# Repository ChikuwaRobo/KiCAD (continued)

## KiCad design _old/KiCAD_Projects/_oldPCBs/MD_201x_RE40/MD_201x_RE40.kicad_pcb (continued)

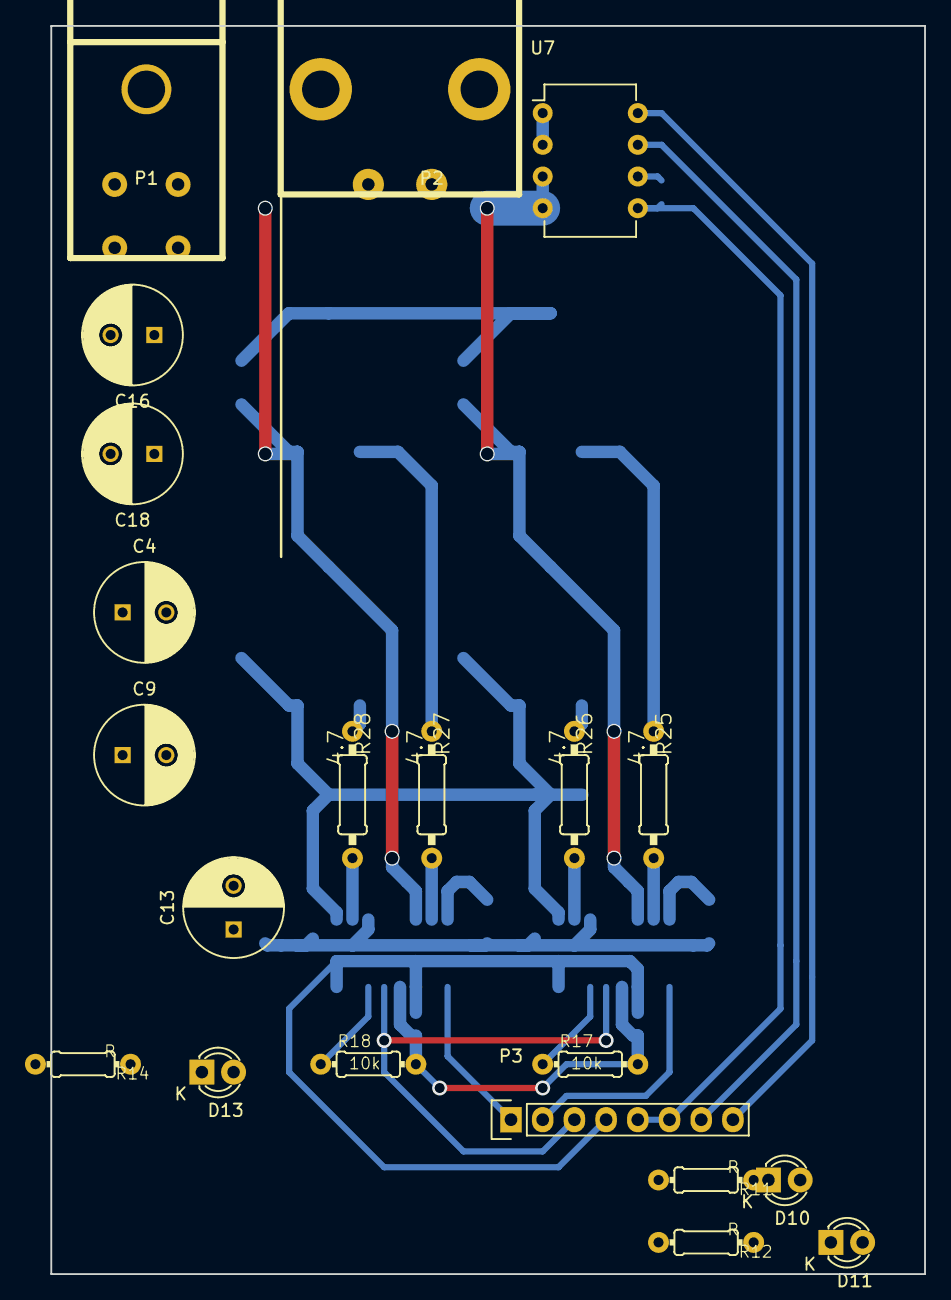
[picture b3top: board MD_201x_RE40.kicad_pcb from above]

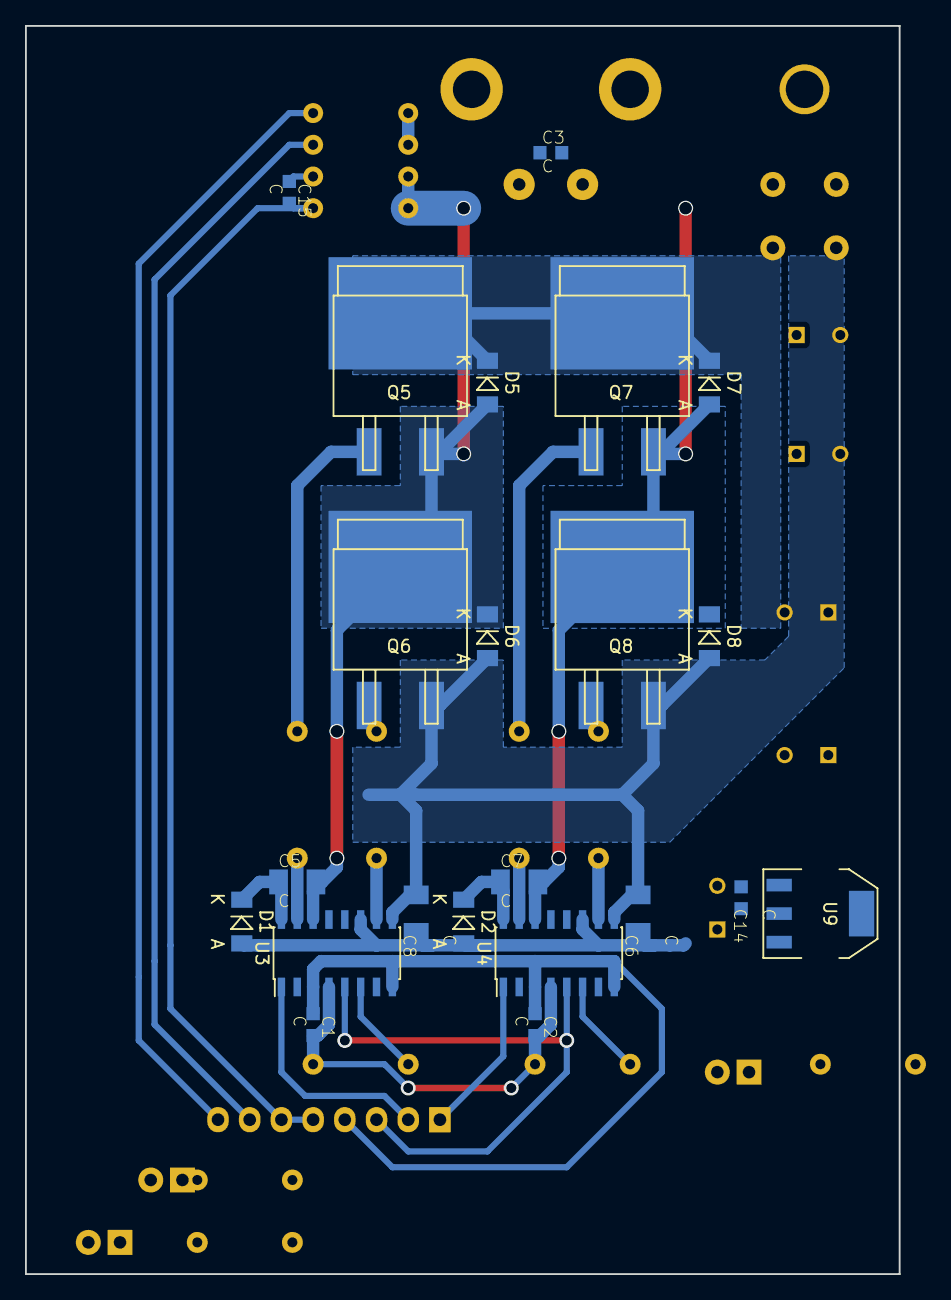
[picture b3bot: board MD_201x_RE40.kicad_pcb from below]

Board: 2 copper layers, 70.0 x 100.0 mm, 43 parts (22 on the bottom side), 29 nets.

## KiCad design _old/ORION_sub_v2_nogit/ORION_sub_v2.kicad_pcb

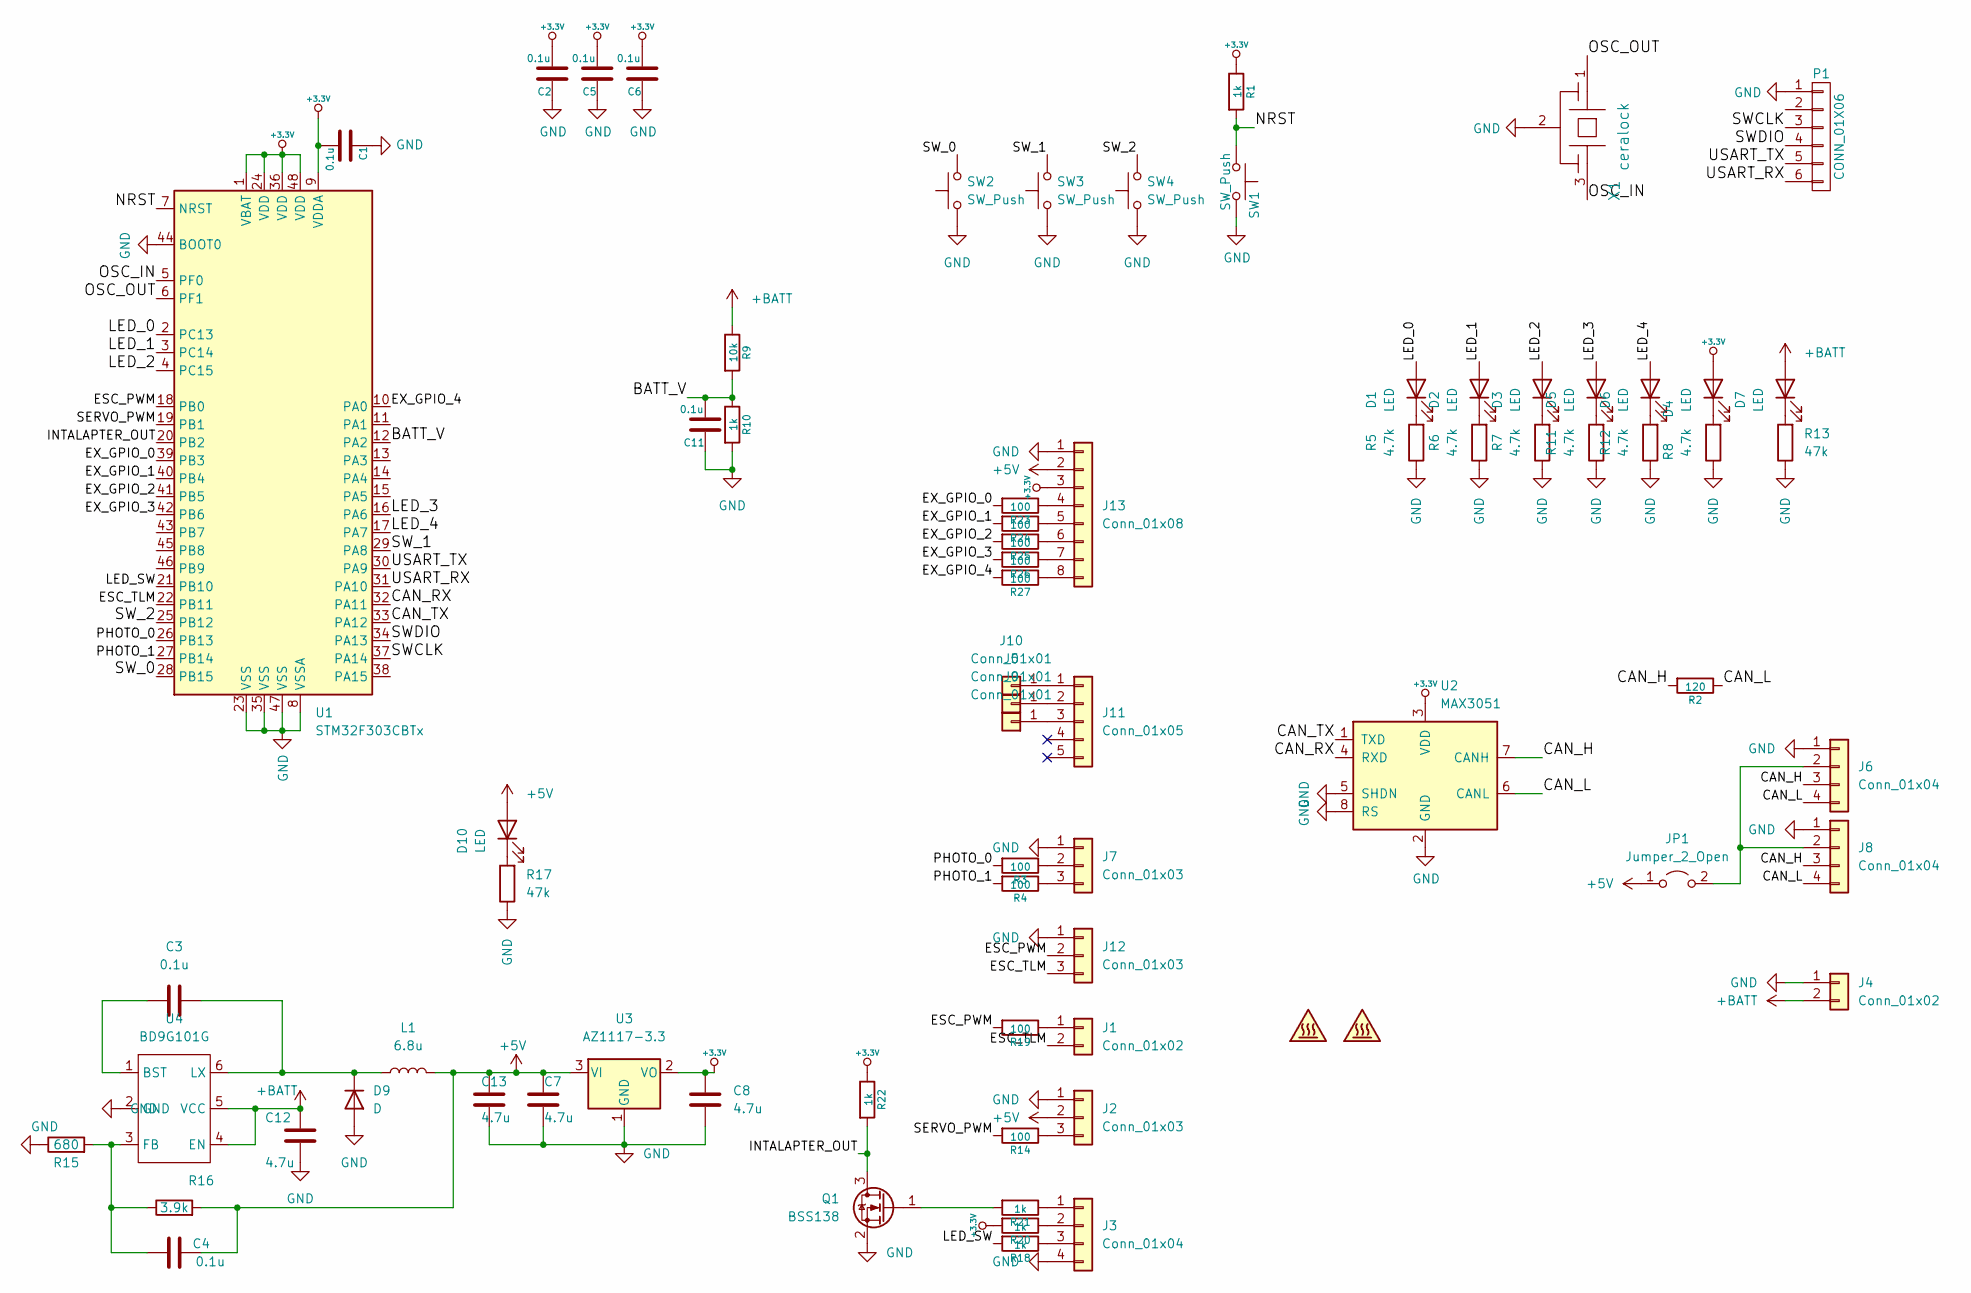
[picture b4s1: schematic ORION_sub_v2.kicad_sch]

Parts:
C1, C2, C5, C6, C11: 0.1u; C_0603_1608Metric
C3, C4: 0.1u; C_0402_1005Metric
C7, C8, C12, C13: 4.7u; C_1206_3216Metric
D1, D2, D3, D4, D5, D6, D7, D10: LED; LED_0603_1608Metric
D9: D; D_PowerDI-123
J1: Conn_01x02; Hirose_DF13-02P-1.25DSA_1x02_P1.25mm_Vertical
J2: Conn_01x03; JST_PH_S3B-PH-K_1x03_P2.00mm_Horizontal
J3, J6, J8: Conn_01x04; Hirose_DF13-04P-1.25DSA_1x04_P1.25mm_Vertical
J4: Conn_01x02; AMASS_XT30PW-M_1x02_P2.50mm_Horizontal
J5, J9, J10: Conn_01x01; WireSoldingPad_PowerTH
J7: Conn_01x03; Hirose_DF13-03P-1.25DSA_1x03_P1.25mm_Vertical
J11: Conn_01x05; 2053380003
J12: Conn_01x03; PinSocket_1x03_P2.54mm_Vertical
J13: Conn_01x08; Hirose_DF13-08P-1.25DSA_1x08_P1.25mm_Vertical
JP1: Jumper_2_Open; SolderJumper-2_P1.3mm_Open_RoundedPad1.0x1.5mm
L1: 6.8u; L_Taiyo-Yuden_NR-50xx
LG1: SYM_Hot_Small; ibis_logo_10x8mm_mask
LG2: SYM_Hot_Small; ibis_logo_10x8mm_silk
P1: CONN_01X06; ZH_B6B-ZR
Q1: BSS138; SOT-23
R1, R10, R18, R20, R21, R22: 1k; R_0603_1608Metric
R2: 120; R_0603_1608Metric
R3, R4, R14, R19, R23, R24, R25, R26, R27: 100; R_0603_1608Metric
R5, R6, R7, R8, R11, R12: 4.7k; R_0603_1608Metric
R9: 10k; R_0603_1608Metric
R13, R17: 47k; R_0603_1608Metric
R15: 680; R_0603_1608Metric
R16: 3.9k; R_0603_1608Metric
SW1, SW2, SW3, SW4: SW_Push; SW_Push_1P1T_NO_CK_KMR2
U1: STM32F303CBTx; LQFP-48_7x7mm_P0.5mm
U2: MAX3051; SO-8_3.9x4.9mm_P1.27mm
U3: AZ1117-3.3; SOT-23
U4: BD9G101G; SOT-23-6
X1: ceralock; Resonator_SMD_Murata_CSTxExxV-3Pin_3.0x1.1mm

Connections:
+3.3V: C1.2, C2.2, C5.2, C6.2, C8.1, D4.2 (A), J13.3, R1.1, R20.2, R22.1, U1.1 (VBAT), U1.9 (VDDA), U1.24 (VDD), U1.36 (VDD), U1.48 (VDD), U2.3 (VDD), U3.2 (VO)
+5V: C4.1, C7.1, C13.1, D10.2 (A), J2.2, J13.2, JP1.1 (A), L1.2, R16.2, U3.3 (VI)
+BATT: C12.1, D7.2 (A), J4.2, R9.1, U4.4 (EN), U4.5 (VCC)
/BATT_V: C11.2, R9.2, R10.1, U1.12 (PA2)
/CAN_H: J6.3, J8.3, R2.2, U2.7 (CANH)
/CAN_L: J6.4, J8.4, R2.1, U2.6 (CANL)
/CAN_RX: U1.32 (PA11), U2.4 (RXD)
/CAN_TX: U1.33 (PA12), U2.1 (TXD)
/ESC_PWM: J12.2, R19.2, U1.18 (PB0)
/ESC_TLM: J1.2, J12.3, U1.22 (PB11)
/EX_GPIO_0: R23.2, U1.39 (PB3)
/EX_GPIO_1: R24.2, U1.40 (PB4)
/EX_GPIO_2: R25.2, U1.41 (PB5)
/EX_GPIO_3: R26.2, U1.42 (PB6)
/EX_GPIO_4: R27.2, U1.10 (PA0)
/INTALAPTER_OUT: Q1.3 (D), R22.2, U1.20 (PB2)
/LED_0: D1.2 (A), U1.2 (PC13)
/LED_1: D2.2 (A), U1.3 (PC14)
/LED_2: D3.2 (A), U1.4 (PC15)
/LED_3: D5.2 (A), U1.16 (PA6)
/LED_4: D6.2 (A), U1.17 (PA7)
/LED_SW: R18.2, U1.21 (PB10)
/NRST: R1.2, SW1.1, U1.7 (NRST)
/OSC_IN: U1.5 (PF0), X1.3
/OSC_OUT: U1.6 (PF1), X1.1
/PHOTO_0: R3.2, U1.26 (PB13)
/PHOTO_1: R4.2, U1.27 (PB14)
/SERVO_PWM: R14.2, U1.19 (PB1)
/SWCLK: P1.3, U1.37 (PA14)
/SWDIO: P1.4, U1.34 (PA13)
/SW_0: SW2.2, U1.28 (PB15)
/SW_1: SW3.2, U1.29 (PA8)
/SW_2: SW4.2, U1.25 (PB12)
/USART_RX: P1.6, U1.31 (PA10)
/USART_TX: P1.5, U1.30 (PA9)
GND: C1.1, C2.1, C5.1, C6.1, C7.2, C8.2, C11.1, C12.2, C13.2, D9.2 (A), J2.1, J3.4, J4.1, J6.1, J7.1, J8.1, J12.1, J13.1, P1.1, Q1.2 (S), R5.1, R6.1, R7.1, R8.1, R10.2, R11.1, R12.1, R13.1, R15.1, R17.1, SW1.2, SW2.1, SW3.1, SW4.1, U1.8 (VSSA), U1.23 (VSS), U1.35 (VSS), U1.44 (BOOT0), U1.47 (VSS), U2.2 (GND), U2.5 (SHDN), U2.8 (RS), U3.1 (GND), U4.2 (GND), X1.2
unnamed: C3.1, D9.1 (K), L1.1, U4.6 (LX)
unnamed: C3.2, U4.1 (BST)
unnamed: C4.2, R15.2, R16.1, U4.3 (FB)
unnamed: D1.1 (K), R5.2
unnamed: D2.1 (K), R6.2
unnamed: D3.1 (K), R7.2
unnamed: D4.1 (K), R8.2
unnamed: D5.1 (K), R11.2
unnamed: D6.1 (K), R12.2
unnamed: D7.1 (K), R13.2
unnamed: D10.1 (K), R17.2
unnamed: J1.1, R19.1
unnamed: J2.3, R14.1
unnamed: J3.1, R21.1
unnamed: J3.2, R20.1
unnamed: J3.3, R18.1
unnamed: J6.2, J8.2, JP1.2 (B)
unnamed: J7.2, R3.1
unnamed: J7.3, R4.1
unnamed: J10.1, J11.1
unnamed: J5.1, J11.2
unnamed: J9.1, J11.3
unnamed: J13.4, R23.1
unnamed: J13.5, R24.1
unnamed: J13.6, R25.1
unnamed: J13.7, R26.1
unnamed: J13.8, R27.1
unnamed: Q1.1 (G), R21.2

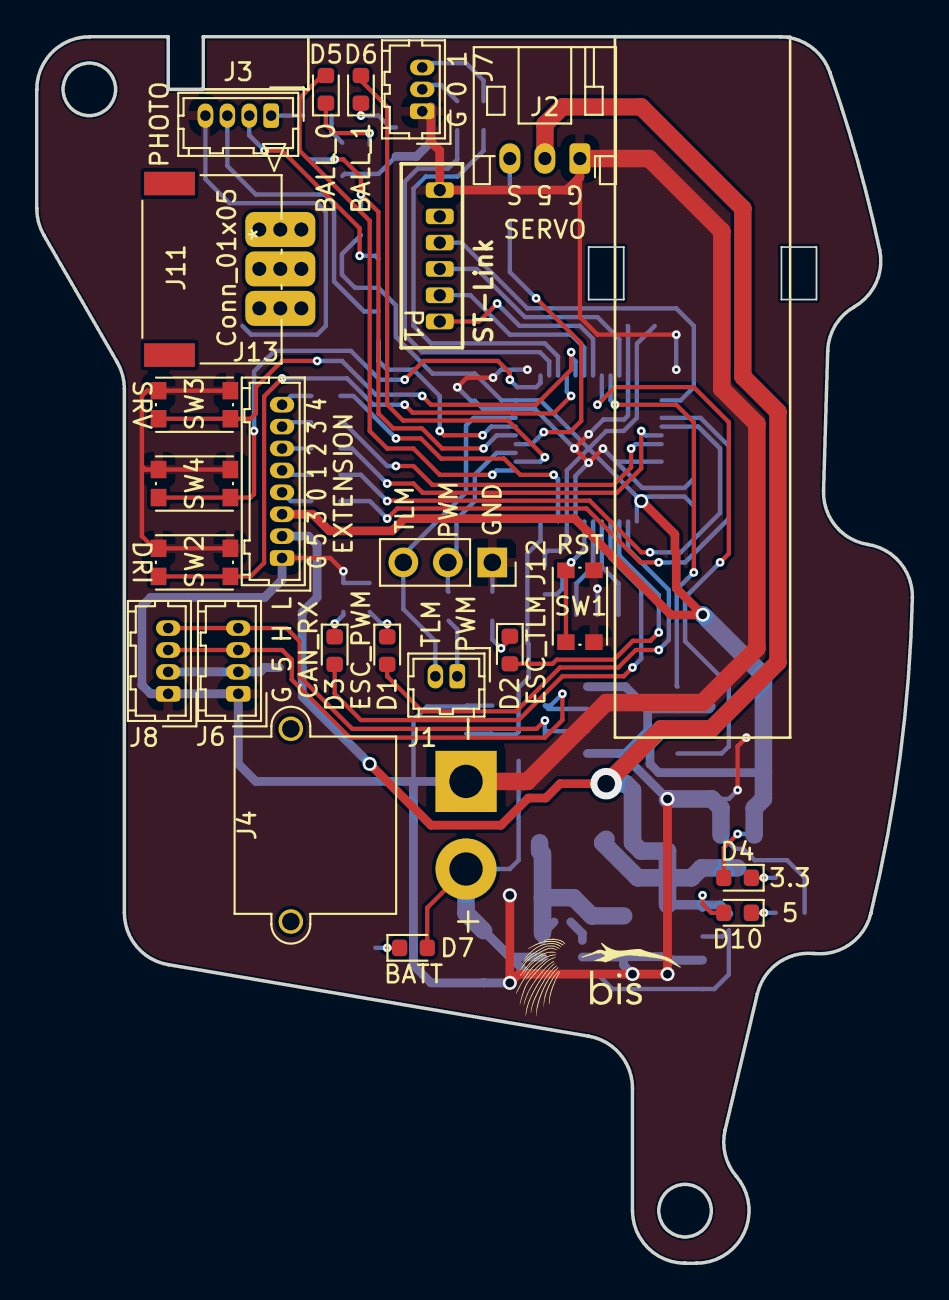
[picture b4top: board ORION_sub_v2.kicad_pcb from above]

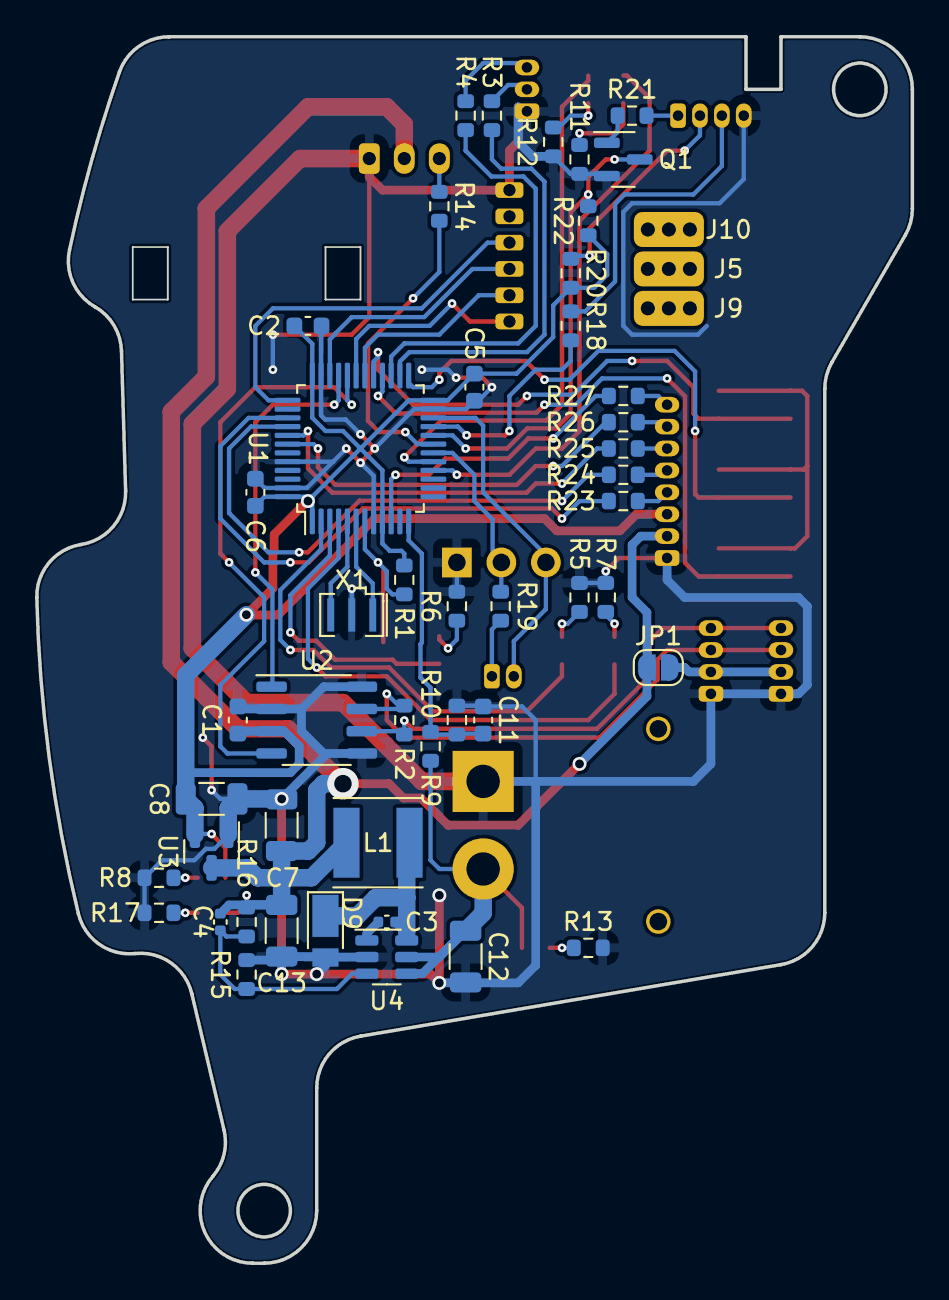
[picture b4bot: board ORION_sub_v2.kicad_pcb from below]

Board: 2 copper layers, 50.0 x 70.0 mm, 75 parts (50 on the bottom side), 64 nets.

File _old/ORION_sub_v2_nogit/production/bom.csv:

Designator,Footprint,Quantity,Value,LCSC Part #
"C1, C11, C2, C5, C6",C_0603_1608Metric,5,0.1u,
"C12, C13, C7, C8",C_1206_3216Metric,4,4.7u,
"C3, C4",C_0402_1005Metric,2,0.1u,
"D1, D10, D2, D3, D4, D5, D6, D7",LED_0603_1608Metric,8,LED,
D9,D_PowerDI-123,1,D,
J1,Hirose_DF13-02P-1.25DSA_1x02_P1.25mm_Vertical,1,Conn_01x02,
"J10, J5, J9",WireSoldingPad_PowerTH,3,Conn_01x01,
J11,2053380003,1,Conn_01x05,
J12,PinSocket_1x03_P2.54mm_Vertical,1,Conn_01x03,
J13,Hirose_DF13-08P-1.25DSA_1x08_P1.25mm_Vertical,1,Conn_01x08,
J2,JST_PH_S3B-PH-K_1x03_P2.00mm_Horizontal,1,Conn_01x03,
"J3, J6, J8",Hirose_DF13-04P-1.25DSA_1x04_P1.25mm_Vertical,3,Conn_01x04,
J4,AMASS_XT30PW-M_1x02_P2.50mm_Horizontal,1,Conn_01x02,
J7,Hirose_DF13-03P-1.25DSA_1x03_P1.25mm_Vertical,1,Conn_01x03,
JP1,SolderJumper-2_P1.3mm_Open_RoundedPad1.0x1.5mm,1,Jumper_2_Open,
L1,L_Taiyo-Yuden_NR-50xx,1,6.8u,
LG1,ibis_logo_10x8mm_mask,1,SYM_Hot_Small,
LG2,ibis_logo_10x8mm_silk,1,SYM_Hot_Small,
P1,ZH_B6B-ZR,1,CONN_01X06,
Q1,SOT-23,1,BSS138,
"R1, R10, R18, R20, R21, R22",R_0603_1608Metric,6,1k,
"R11, R12, R5, R6, R7, R8",R_0603_1608Metric,6,4.7k,
"R13, R17",R_0603_1608Metric,2,47k,
"R14, R19, R23, R24, R25, R26, R27, R3, R4",R_0603_1608Metric,9,100,
R15,R_0603_1608Metric,1,680,
R16,R_0603_1608Metric,1,3.9k,
R2,R_0603_1608Metric,1,120,
R9,R_0603_1608Metric,1,10k,
"SW1, SW2, SW3, SW4",SW_Push_1P1T_NO_CK_KMR2,4,SW_Push,
U1,LQFP-48_7x7mm_P0.5mm,1,STM32F303CBTx,
U2,SO-8_3.9x4.9mm_P1.27mm,1,MAX3051,
U3,SOT-23,1,AZ1117-3.3,
U4,SOT-23-6,1,BD9G101G,
X1,Resonator_SMD_Murata_CSTxExxV-3Pin_3.0x1.1mm,1,ceralock,

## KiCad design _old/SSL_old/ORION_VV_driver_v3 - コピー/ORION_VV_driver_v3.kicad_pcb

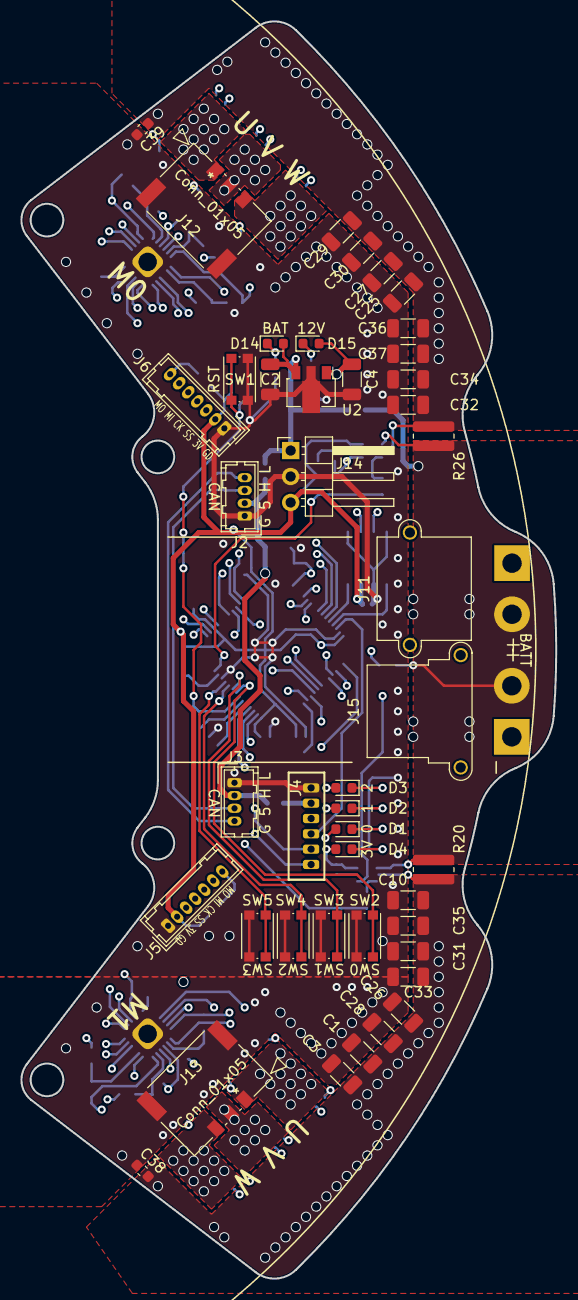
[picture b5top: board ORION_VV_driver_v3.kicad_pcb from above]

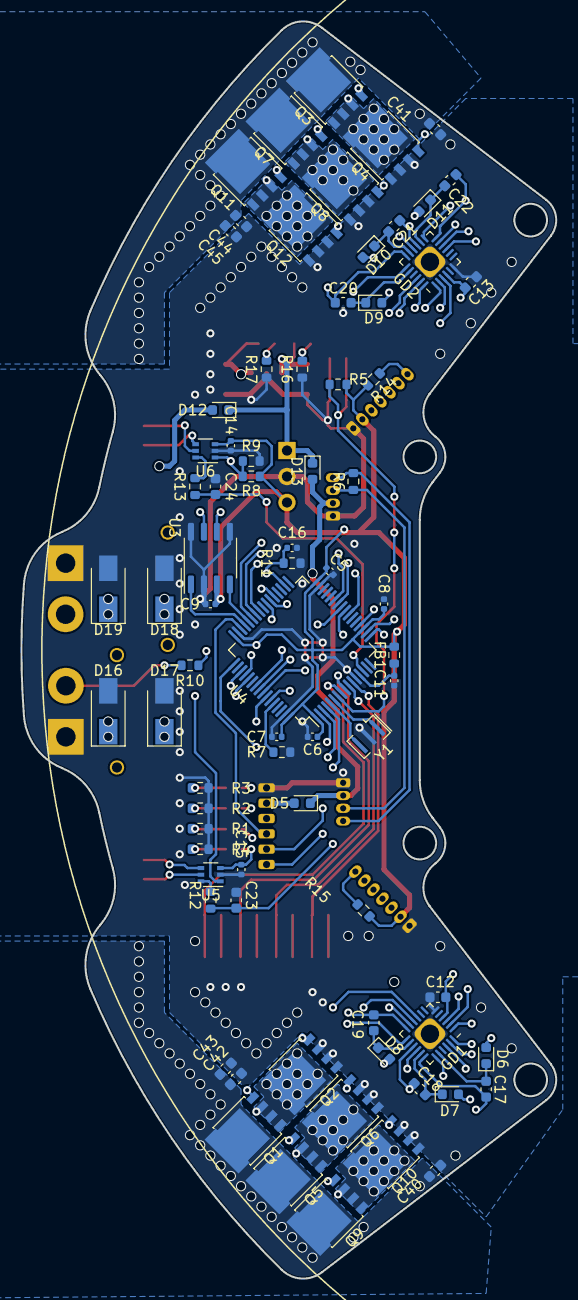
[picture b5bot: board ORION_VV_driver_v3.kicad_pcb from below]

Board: 4 copper layers, 52.4 x 123.1 mm, 119 parts (75 on the bottom side), 84 nets.

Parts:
C1, C2, C3, C4, C10, C25, C26, C27, C28, C29, C30, C31, C32, C33, C34, C35, C36, C37: 4.7u; C_1206_3216Metric
C5, C6, C7, C8, C9, C11, C14, C15, C16: 0.1u; C_0402_1005Metric
C12, C13, C38, C39, C40, C41, C42, C43, C44, C45: 0.1u; C_0603_1608Metric
C17, C18, C19, C20, C21, C22, C23, C24: 1u; C_0603_1608Metric
D1, D2, D3, D4, D14, D15: LED; LED_0603_1608Metric
D5, D6, D7, D8, D9, D10, D11, D12, D13: D; D_0603_1608Metric
D16, D17, D18, D19: D_Zener; D_SMA
FB1: FB100; R_0603_1608Metric
GD1, GD2: FD6288Q; QFN-24-1EP_4x4mm_P0.5mm_EP2.6x2.6mm_Thhole_v2
J2, J3: Conn_01x04; Hirose_DF13-04P-1.25DSA_1x04_P1.25mm_Vertical
J4: Conn_01x06; ZH_B6B-ZR
J5, J6: Conn_01x07; Hirose_DF13-07P-1.25DSA_1x07_P1.25mm_Vertical
J11: Conn_01x02; AMASS_XT30PW-M_1x02_P2.50mm_Horizontal
J12, J13: Conn_01x05; 2053380003
J14: Conn_01x03; PinHeader_1x03_P2.54mm_Horizontal
J15: Conn_01x02; AMASS_XT30PW-F_1x02_P2.50mm_Horizontal
Q1, Q2, Q3, Q4, Q5, Q6, Q7, Q8, Q9, Q10, Q11, Q12: IRF8721PBF-1; LFPAK56
R1, R2, R3, R4: 4.7k; R_0603_1608Metric
R5, R7, R11: 1k; R_0603_1608Metric
R6: 120; R_0603_1608Metric
R8, R9, R12, R13: 100; R_0603_1608Metric
R10, R14, R15: 10k; R_0603_1608Metric
R16, R17: 47k; R_0603_1608Metric
R20, R26: 10m; R_0815_2038Metric
SW1, SW2, SW3, SW4, SW5: SW_Push; SW_Push_1P1T_NO_CK_KMR2
U2: L78L15_SOT89; SOT-89-3
U3: MAX3051; SO-8_3.9x4.9mm_P1.27mm
U4: LQFP-64_10x10mm_P0.5mm
U5, U6: INA199; SOT-363_SC-70-6
Y1: Resonator; Resonator_SMD_Murata_CSTxExxV-3Pin_3.0x1.1mm

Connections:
+3V3: C5.2, C6.2, C7.2, C8.2, C9.2, C14.2, C15.2, D4.2 (A), FB1.1, J5.2, J6.2, J14.3, R5.2, R8.1, R14.2, R15.2, U3.3 (VDD), U4.1 (VBAT), U4.19 (VDD), U4.32 (VDD), U4.48 (VDD), U4.64 (VDD), U5.3 (VDD), U6.3 (VDD)
+5V: D5.1 (K), D13.2 (A), J2.2, J3.2
+12V: C4.2, C12.2, C13.2, D6.2 (A), D7.2 (A), D8.2 (A), D9.2 (A), D10.2 (A), D11.2 (A), D15.2 (A), GD1.4 (VCC), GD2.4 (VCC), U2.1 (OUT)
+BATT: D12.2 (A), D16.1 (K), D17.1 (K), D18.1 (K), D19.1 (K), J11.2, J15.2, R10.1, R20.1, R26.1, U5.4 (IN+), U6.4 (IN+)
/3V3_HARF_REF: R8.2, R9.1, U5.1 (REF), U6.1 (REF)
/BATT_V_SENS: C16.2, R10.2, R11.1, U4.34 (PB13)
/CAN_H: J2.3, J3.3, R6.1, U3.7 (CANH)
/CAN_L: J2.4, J3.4, R6.2, U3.6 (CANL)
/CAN_RX: U3.4 (RXD), U4.44 (PA11)
/CAN_TX: U3.1 (TXD), U4.45 (PA12)
/LED_0: D1.2 (A), U4.2 (PC13)
/LED_1: D2.2 (A), U4.3 (PC14)
/LED_2: D3.2 (A), U4.4 (PC15)
/M0_CS: C24.2, R13.1, U4.14 (PA0)
/M0_CSL: C25.1, C27.1, C29.1, C30.1, C32.1, C34.1, C36.1, C37.1, C39.2, C41.2, C44.2, C45.2, Q3.5 (D), Q7.5 (D), Q11.5 (D), R26.2, U6.5 (IN-)
/M0_U: C22.1, GD2.12 (VS3), J12.1, Q3.1 (S), Q3.2 (S), Q3.3 (S), Q4.5 (D)
/M0_UH: GD2.22 (HIN1), U4.41 (PA8)
/M0_UL: GD2.1 (LIN1), U4.23 (PA7)
/M0_V: C21.1, GD2.15 (VS2), J12.2, Q7.1 (S), Q7.2 (S), Q7.3 (S), Q8.5 (D)
/M0_VH: GD2.23 (HIN2), U4.42 (PA9)
/M0_VL: GD2.2 (LIN2), U4.26 (PB0)
/M0_W: C20.1, GD2.18 (VS1), J12.3, Q11.1 (S), Q11.2 (S), Q11.3 (S), Q12.5 (D)
/M0_WH: GD2.24 (HIN3), U4.43 (PA10)
/M0_WL: GD2.3 (LIN3), U4.27 (PB1)
/M1_CS: C23.2, R12.1, U4.20 (PA4)
/M1_CSL: C1.1, C3.1, C10.1, C26.1, C28.1, C31.1, C33.1, C35.1, C38.2, C40.2, C42.2, C43.2, Q1.5 (D), Q5.5 (D), Q9.5 (D), R20.2, U5.5 (IN-)
/M1_U: C19.1, GD1.12 (VS3), J13.1, Q1.1 (S), Q1.2 (S), Q1.3 (S), Q2.5 (D)
/M1_UH: GD1.22 (HIN1), U4.37 (PC6)
/M1_UL: GD1.1 (LIN1), U4.51 (PC10)
/M1_V: C18.1, GD1.15 (VS2), J13.2, Q5.1 (S), Q5.2 (S), Q5.3 (S), Q6.5 (D)
/M1_VH: GD1.23 (HIN2), U4.38 (PC7)
/M1_VL: GD1.2 (LIN2), U4.52 (PC11)
/M1_W: C17.1, GD1.18 (VS1), J13.3, Q9.1 (S), Q9.2 (S), Q9.3 (S), Q10.5 (D)
/M1_WH: GD1.24 (HIN3), U4.39 (PC8)
/M1_WL: GD1.3 (LIN3), U4.53 (PC12)
/NRST: R5.1, SW1.2, U4.7 (NRST)
/NSS_ENC0: J5.3, U4.58 (PB6)
/NSS_ENC1: J6.3, U4.59 (PB7)
/OSC_IN: U4.5 (PF0), Y1.3
/OSC_OUT: U4.6 (PF1), Y1.1
/SPI_CLK: J5.4, J6.4, U4.55 (PB3)
/SPI_MISO: J5.5, J6.5, U4.56 (PB4)
/SPI_MOSI: J5.6, J6.6, U4.57 (PB5)
/SW0: SW2.2, U4.8 (PC0)
/SW1: SW3.2, U4.9 (PC1)
/SW2: SW4.2, U4.10 (PC2)
/SW3: SW5.2, U4.11 (PC3)
/SWCLK: J4.3, U4.49 (PA14)
/SWDIO: J4.4, U4.46 (PA13)
/TEMP_0: J5.7, R15.1, U4.17 (PA3)
/TEMP_1: J6.7, R14.1, U4.18 (PF4)
/UART1_RX: J4.6, U4.25 (PC5)
/UART1_TX: J4.5, U4.24 (PC4)
GND: C1.2, C2.1, C3.2, C4.1, C5.1, C6.1, C7.1, C8.1, C9.1, C10.2, C11.1, C12.1, C13.1, C14.1, C15.1, C16.1, C23.1, C24.1, C25.2, C26.2, C27.2, C28.2, C29.2, C30.2, C31.2, C32.2, C33.2, C34.2, C35.2, C36.2, C37.2, C38.1, C39.1, C40.1, C41.1, C42.1, C43.1, C44.1, C45.1, D16.2 (A), D17.2 (A), D18.2 (A), D19.2 (A), GD1.6 (COM), GD1.25 (PAD), GD2.6 (COM), GD2.25 (PAD), J2.1, J3.1, J4.1, J5.1, J6.1, J11.1, J12.4, J12.5, J13.4, J13.5, J14.2, J15.1, Q2.1 (S), Q2.2 (S), Q2.3 (S), Q4.1 (S), Q4.2 (S), Q4.3 (S), Q6.1 (S), Q6.2 (S), Q6.3 (S), Q8.1 (S), Q8.2 (S), Q8.3 (S), Q10.1 (S), Q10.2 (S), Q10.3 (S), Q12.1 (S), Q12.2 (S), Q12.3 (S), R1.1, R2.1, R3.1, R4.1, R7.1, R9.2, R11.2, R16.1, R17.1, SW1.1, SW2.1, SW3.1, SW4.1, SW5.1, U2.2 (GND), U3.2 (GND), U3.5 (SHDN), U3.8 (RS), U4.12 (VSSA), U4.31 (VSS), U4.47 (VSS), U4.63 (VSS), U5.2 (GND), U6.2 (GND), Y1.2
unnamed: C2.2, D12.1 (K), D13.1 (K), D14.2 (A), J14.1, U2.3 (IN)
unnamed: C11.2, FB1.2, U4.13 (VDDA)
unnamed: C17.2, D6.1 (K), GD1.20 (VB1)
unnamed: C18.2, D7.1 (K), GD1.17 (VB2)
unnamed: C19.2, D8.1 (K), GD1.14 (VB3)
unnamed: C20.2, D9.1 (K), GD2.20 (VB1)
unnamed: C21.2, D10.1 (K), GD2.17 (VB2)
unnamed: C22.2, D11.1 (K), GD2.14 (VB3)
unnamed: D1.1 (K), R1.2
unnamed: D2.1 (K), R2.2
unnamed: D3.1 (K), R3.2
unnamed: D4.1 (K), R4.2
unnamed: D5.2 (A), J4.2
unnamed: D14.1 (K), R16.2
unnamed: D15.1 (K), R17.2
unnamed: GD1.9 (LO3), Q2.4 (G)
unnamed: GD1.10 (LO2), Q6.4 (G)
unnamed: GD1.11 (LO1), Q10.4 (G)
unnamed: GD1.13 (HO3), Q1.4 (G)
unnamed: GD1.16 (HO2), Q5.4 (G)
unnamed: GD1.19 (HO1), Q9.4 (G)
unnamed: GD2.9 (LO3), Q4.4 (G)
unnamed: GD2.10 (LO2), Q8.4 (G)
unnamed: GD2.11 (LO1), Q12.4 (G)
unnamed: GD2.13 (HO3), Q3.4 (G)
unnamed: GD2.16 (HO2), Q7.4 (G)
unnamed: GD2.19 (HO1), Q11.4 (G)
unnamed: R7.2, U4.60 (BOOT0)
unnamed: R12.2, U5.6 (OUT)
unnamed: R13.2, U6.6 (OUT)

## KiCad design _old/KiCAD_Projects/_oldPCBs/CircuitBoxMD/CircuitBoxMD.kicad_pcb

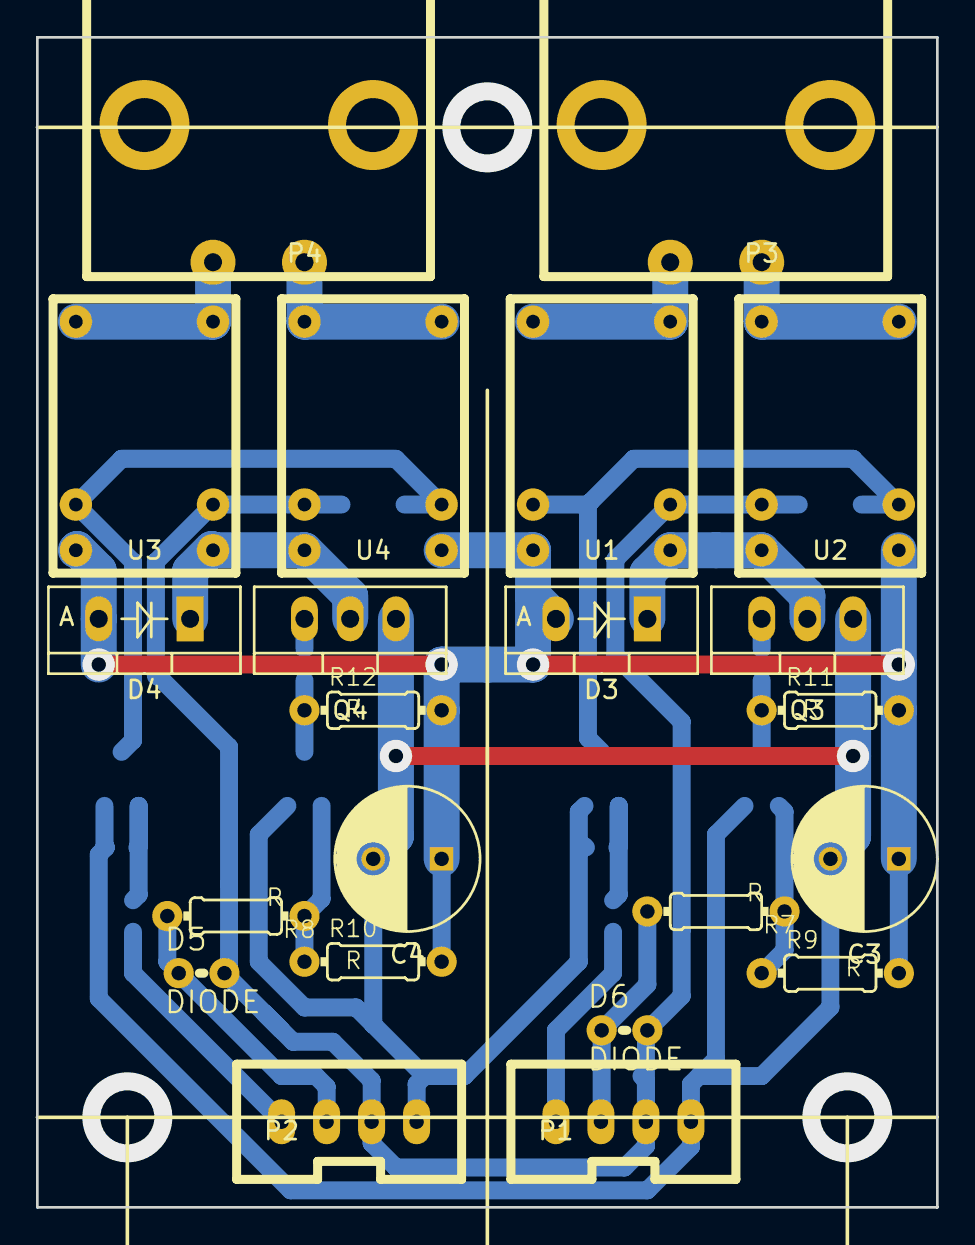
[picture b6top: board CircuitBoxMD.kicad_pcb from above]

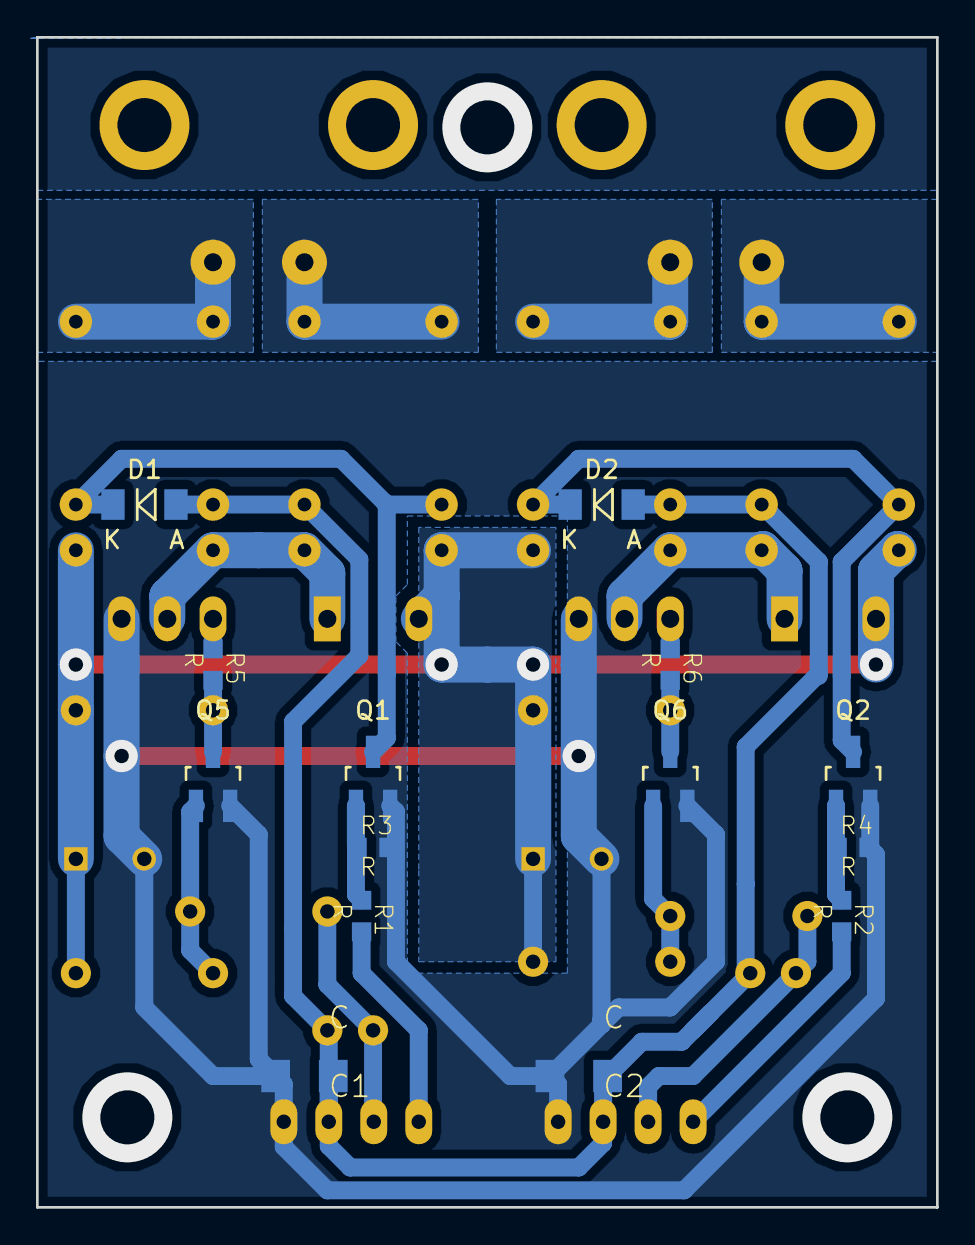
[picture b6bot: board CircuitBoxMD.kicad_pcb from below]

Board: 2 copper layers, 50.0 x 65.0 mm, 36 parts (14 on the bottom side), 23 nets.

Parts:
C1, C2: C; C3216
C3, C4: C; C_Radial_D8_L21_P3.8
D1, D2: DIODE; MiniMELF_Standard
D3, D4: DIODE; Diode_TO-220_Vertical
D5, D6: DIODE; 0204_V
P1, P2: CONN_4; XA_4T
P3, P4: CONN_2; D-3200S_2
Q1, Q2, Q5, Q6: MOS_N; SOT-23_Handsoldering
Q3, Q4: MOS_N; TO-220_Neutral123_Vertical
R1, R2, R3, R4, R5, R6: R; C0603K
R7, R8, R9, R10, R11, R12: R; 0204_2f7
U1, U2, U3, U4: HSIN_946

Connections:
+5V: C1.1, C2.1, D1.2, D2.2, D5.2, D6.2, P1.2, P2.2, U1.5, U2.2, U3.5, U4.2
+BATT: C3.1, C4.1, D3.2, D4.2, R9.2, R10.2, R11.2, R12.2, U1.3, U2.4, U3.3, U4.4
COIL0: D1.1, Q1.D, U1.2, U2.5
COIL1: D2.1, Q2.D, U3.2, U4.5
GND: C1.2, C2.2, C3.2, C4.2, P1.1, P2.1, Q1.S, Q2.S, Q3.S, Q4.S, Q5.S, Q6.S, R3.2, R4.2
unnamed: D5.1, P2.3, R8.2
unnamed: D6.1, P1.3, R7.2
unnamed: P1.4, R1.2
unnamed: P2.4, R2.2
unnamed: P3.1, U2.1
unnamed: P3.2, U1.1
unnamed: P4.1, U4.1
unnamed: P4.2, U3.1
unnamed: Q1.G, R1.1, R3.1
unnamed: Q2.G, R2.1, R4.1
unnamed: Q3.G, R5.1
unnamed: Q4.G, R6.1
unnamed: Q5.D, R5.2, R11.1
unnamed: Q5.G, R7.1, R9.1
unnamed: Q6.D, R6.2, R12.1
unnamed: Q6.G, R8.1, R10.1
PWM_GND0: D3.1, Q3.D, U1.4, U2.3
PWM_GND1: D4.1, Q4.D, U3.4, U4.3
